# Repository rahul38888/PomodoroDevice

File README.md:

# PomodoroDevice

## 7 segments leds

## 4x7 segment display pinout diagram

## Shift register 74HC595

## Pins connections
| 4x7 pins | Arduino pins |
|-|-|
|D1 (Through 220 Ω)|2|
|D2 (Through 220 Ω)|3|
|D3 (Through 220 Ω)|4|
|D4 (Through 220 Ω)|5|

| 4x7 pins | 74HC595 pins |
|-|-|
|A|Q0|
|B|Q1|
|C|Q2|
|D|Q3|
|E|Q4|
|F|Q5|
|G|Q6|
|DP|Q7|

| Arduino pins | 74HC595 pins |
|-|-|
|GND|GND|
|5V|Vcc|
|11|DS|
|GND|OE|
|8|ST_CP|
|12|SH_CP|
|5V|MR|

## Bytes to Character mapping
|Character|Byte value (ABCDEFG)|Integer value|
|-|-|-|
|0|0000001|1|
|1|1001111|79|
|2|0010010|18|
|3|0000110|6|
|4|1001100|76|
|5|0100100|36|
|6|0100000|32|
|7|0001111|15|
|8|0000000|0|
|9|0000100|4|
|Blacnk|1111111|127|

1 means inactive and 0 means active.

**74HC595** need to have 8 bits written into it. The 1st place bit will decide state of **DP**. That is being added on runtime.

## Circuit diagrams

## 3D plates

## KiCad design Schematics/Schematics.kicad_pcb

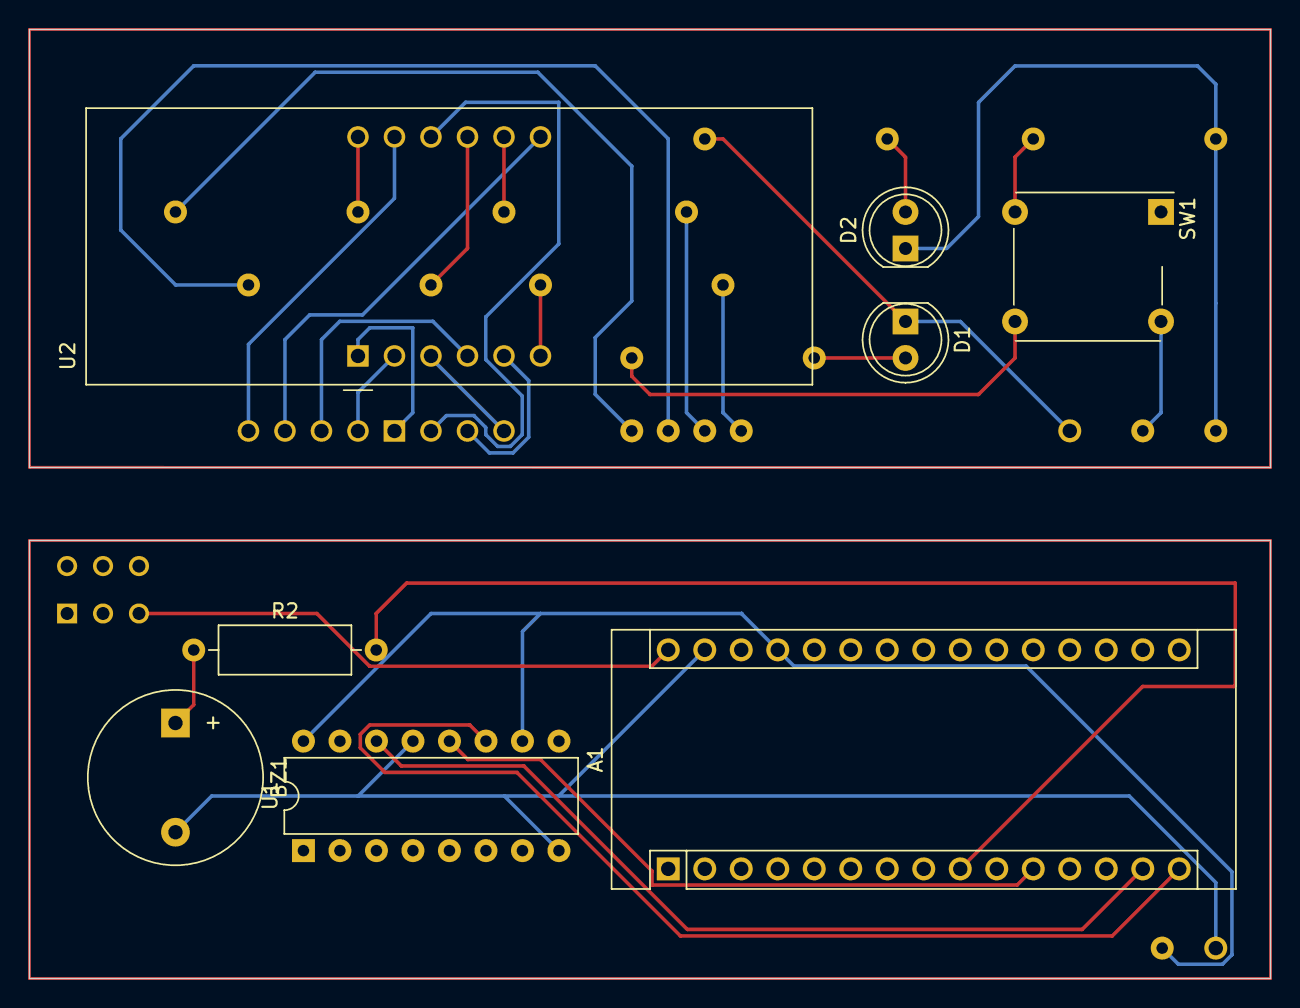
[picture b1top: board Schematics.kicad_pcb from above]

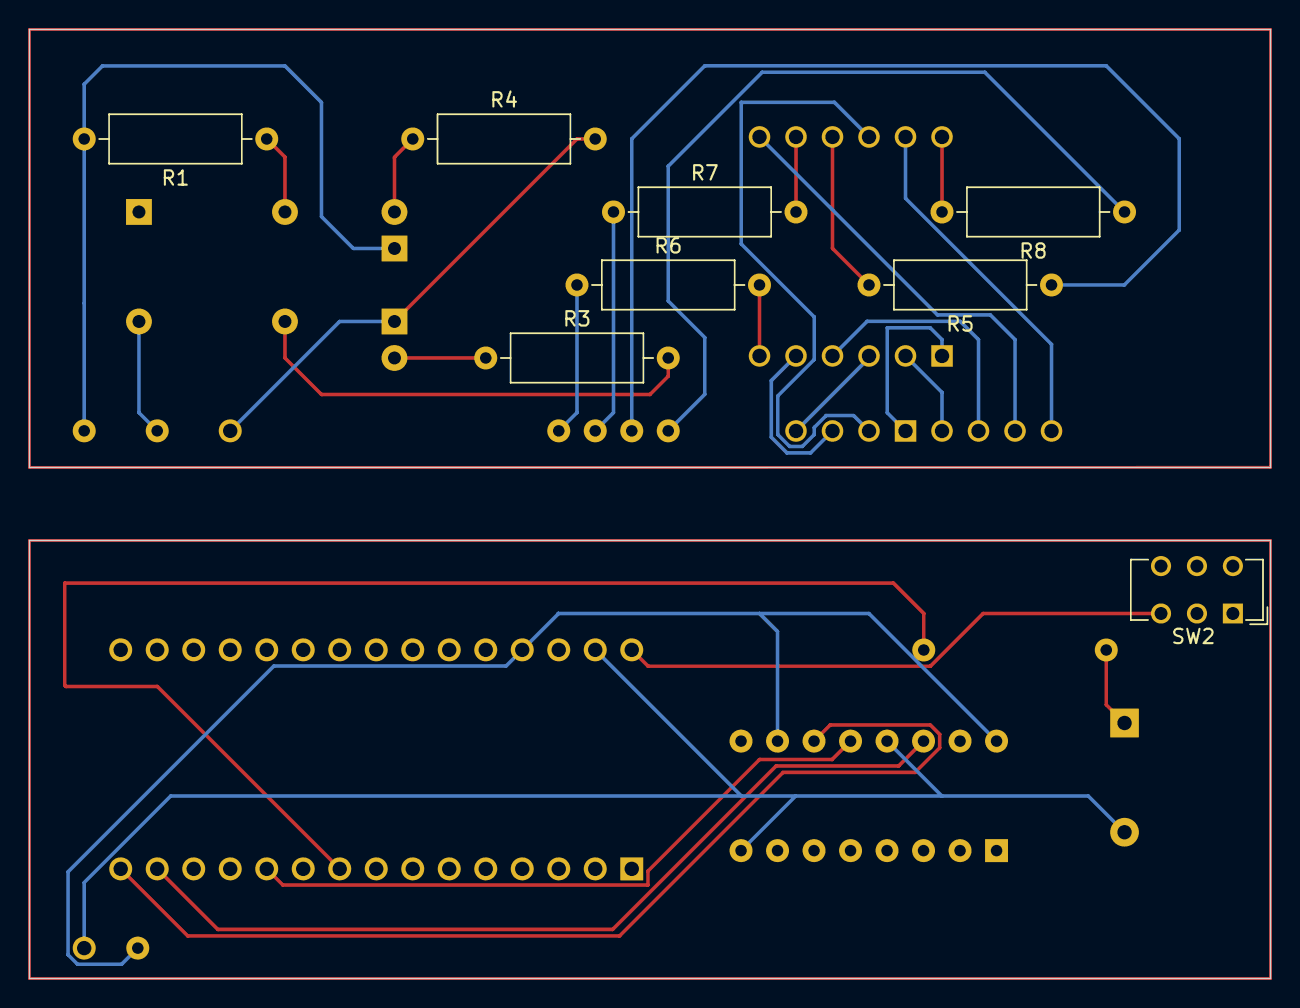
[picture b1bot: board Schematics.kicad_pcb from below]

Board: 2 copper layers, 86.4 x 66.0 mm, 16 parts (8 on the bottom side), 28 nets.

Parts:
A1: Arduino_Nano_v3.x; Arduino_Nano
BZ1: Buzzer; Buzzer_12x9.5RM7.6
D1: Green; LED_D5.0mm
D2: Orange; LED_D5.0mm
R1, R3, R4, R5, R6, R7, R8: R 220; R_Axial_DIN0309_L9.0mm_D3.2mm_P12.70mm_Horizontal
R2: R 100; R_Axial_DIN0309_L9.0mm_D3.2mm_P12.70mm_Horizontal
SW1: SW_MEC_5E; SW_MEC_5GTH9
SW2: SW_DPDT_x2; SW_CuK_JS202011CQN_DPDT_Straight
U1: 74HC595; DIP-16_W7.62mm
U2: CC56-12YWA

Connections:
Dat1: A1.5 (D2), R8.1
Dat2: A1.6 (D3), R5.1
Dat3: A1.7 (D4), R7.1
Dat4: A1.8 (D5), R6.1
GND: BZ1.2 (+), D2.1 (K), R1.2, U1.8 (GND), U1.13 (~OE)
unnamed: A1.9 (D6), R2.2
unnamed: A1.12 (D9), D1.1 (K), R4.2
unnamed: A1.27 (+5V), R3.2, SW1.2, U1.10 (~SRCLR), U1.16 (VCC)
unnamed: A1.30 (VIN), SW2.3 (C)
unnamed: BZ1.1 (-), R2.1
unnamed: D1.2 (A), R3.1
unnamed: D2.2 (A), R4.1
unnamed: R1.1, SW1.1
unnamed: R5.2, U2.9 (CC2)
unnamed: R6.2, U2.6 (CC4)
unnamed: R7.2, U2.8 (CC3)
unnamed: R8.2, U2.12 (CC1)
unnamed: U1.1 (QB), U2.7 (b)
unnamed: U1.2 (QC), U2.4 (c)
unnamed: U1.3 (QD), U2.2 (d)
unnamed: U1.4 (QE), U2.1 (e)
unnamed: U1.5 (QF), U2.10 (f)
unnamed: U1.6 (QG), U2.5 (g)
unnamed: U1.7 (QH), U2.3 (DPX)
unnamed: U1.15 (QA), U2.11 (a)
RCLK: A1.11 (D8), U1.12 (RCLK)
SER: A1.14 (D11), U1.14 (SER)
SRCLK: A1.15 (D12), U1.11 (SRCLK)

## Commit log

2021-12-28 Timer + ender programm working. Without buttons and buzzer
2021-12-29 Working: Buzzer, Button, Pomodoro sequance, IsWorking status with 2 leds
2021-12-29 minor
2021-12-29 media
2021-12-30 Curcuit digrams
2022-01-01 Schematics using KiCad
2022-01-14 Final Kicad changes
2022-01-26 new fucntion in device
